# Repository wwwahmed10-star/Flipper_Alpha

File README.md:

# Flipper Alpha - KiCad Files

Files generated from the uploaded schematic and PCB images:
- `Flipper_Alpha.kicad_sch` — Complete schematic (KiCad 8)
- `Flipper_Alpha.kicad_pcb` — PCB layout ready for routing (KiCad 8)

The symbols and footprints are **embedded in the files themselves** — no external libraries are required.

## Pin Mapping

| Module | Signal | ESP32 (CYD) | Notes |
|---|---|---|---|
| PN532 (I2C) | SDA / SCL | GPIO21 / GPIO22 | 3.3V power |
| CC1101 (SPI) | SCK / MISO / MOSI | GPIO18 / GPIO19 / GPIO23 | Shared SPI |
| CC1101 | CSN / GDO0 / GDO2 | GPIO5 / GPIO2 / GPIO35 | |
| NRF24L01 (SPI) | SCK / MISO / MOSI | GPIO18 / GPIO19 / GPIO23 | Shared SPI |
| NRF24L01 | CE / CSN | GPIO26 / GPIO25 | |
| IR LED | Output | GPIO4 through a 220Ω resistor | LED to GND |
| TSOP (IR RX) | OUT | GPIO34 | |
| 433MHz RF | TX / RX | GPIO12 / GPIO13 | 5V power |
| GPS (UART) | TX / RX | GPIO16 / GPIO17 | UART2 |

## Important Assumptions (Review Before Manufacturing!)

1. Some connections in the original image are not completely clear. The most logical pin assignments were used (based on the conventional Flipper Zero layout).
2. The PCB is **unrouted**: the components are placed and the nets are defined. Open the board in KiCad and route the tracks manually or with FreeRouting.
3. Verify the exact pinout of your CYD-24325028 display version before fabrication.
4. J1–J4 (XH connectors) have been left unconnected. Assign them according to your firmware's button or expansion requirements.
5. The board dimensions are 125 × 85 mm, with four M3 mounting holes.

## KiCad Workflow

1. Open `Flipper_Alpha.kicad_sch` and run the ERC (Electrical Rules Checker).
2. Open `Flipper_Alpha.kicad_pcb`, press **B** to refill the copper zones, then route the nets.

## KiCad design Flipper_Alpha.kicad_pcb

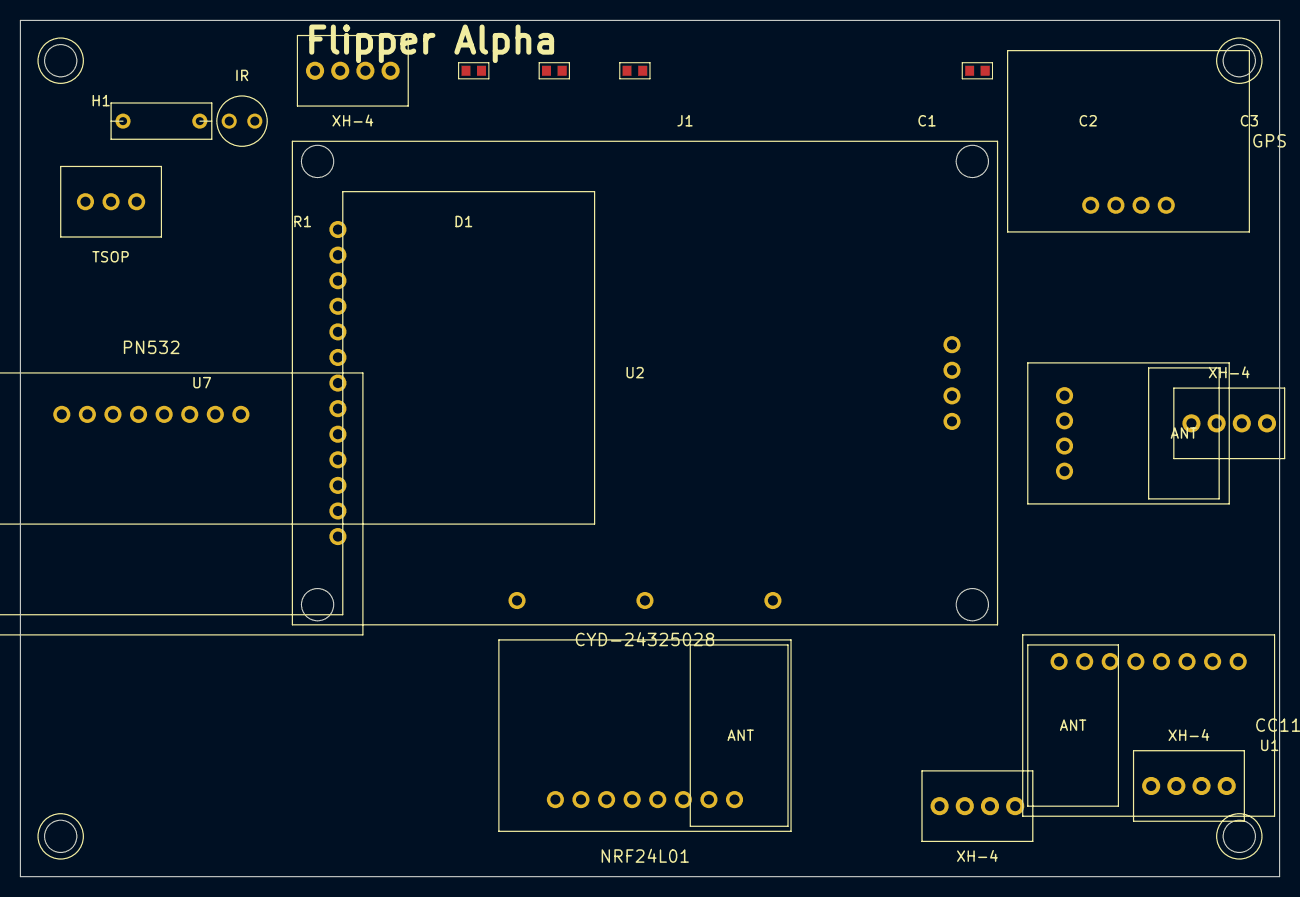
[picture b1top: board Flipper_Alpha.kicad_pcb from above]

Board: 2 copper layers, 125.0 x 85.0 mm, 21 parts (0 on the bottom side), 19 nets, no tracks yet.

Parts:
C1, C2, C3, C4: 100nF; C_0603
D1: IR_LED; LED_IR_5mm
H1, H2, H3, H4: MountingHole; MountingHole_3.2mm
J1, J2, J3, J4: Conn_01x04; XH_4
R1: 220; R_Axial_0207
U1: Module_CYD; CYD_24325028
U2: Module_PN532; PN532_I2C
U3: Module_CC1101; CC1101
U4: Module_NRF24L01; NRF24L01
U5: Module_RF433; RF433
U6: Module_GPS; GPS
U7: Module_TSOP; TSOP_IR

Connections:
+3V3: C1.1, C2.1, C3.1, C4.1, U1.3V3, U2.3V3, U3.3V3, U4.3V3, U6.3V3, U7.3V3
+5V: U1.5V, U5.5V
GND: C1.2, C2.2, C3.2, C4.2, D1.K, U1.GND, U2.GND, U3.GND, U4.GND, U5.GND, U6.GND, U7.GND
GPIO2: U1.2, U3.GDO0
GPIO4: D1.A, R1.1, R1.2, U1.4
GPIO5: U1.5, U3.CSN
GPIO12: U1.12, U5.DATA_TX
GPIO13: U1.13, U5.DATA_RX
GPIO16: U1.16, U6.TX
GPIO17: U1.17, U6.RX
GPIO18: U1.18, U3.SCK, U4.SCK
GPIO19: U1.19, U3.MISO, U4.MISO
GPIO21: U1.21, U2.SDA
GPIO22: U1.22, U2.SCL
GPIO23: U1.23, U3.MOSI, U4.MOSI
GPIO25: U1.25, U4.CSN
GPIO26: U1.26, U4.CE
GPIO34: U1.34, U7.OUT
GPIO35: U1.35, U3.GDO2
